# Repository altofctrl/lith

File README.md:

## the oldest tool we know how to make

1931, Olduvai Gorge, Tanzania.

In a ravein cut through the Serengeti plain, researchers discovered stones that had been deliberately broken, intentionally struck with larger ones till sharp flakes came away. They call this era of tool making **Oldowan** after the gorge, and it has examples dating back to 2.6 million years ago.

A stone chopper is the simplest
thing that is unmistakably *made*, and for most of the time there have been
hominins at all, it was the most complicated thing anyone could do. Making one
is harder than it looks: you have to read the stone, find a platform, and strike
at an angle that takes a flake off rather than shattering the core. People who
try it without being shown mostly fail.

These tools are some of the simplest things that can be unmistakably *made*, for most of the time we've been about it was the most complicated thing anyone could do.
However making one takes some skill, finding the right stone, striking the right angle with enough force to flake off instead of shatter.

_Knapping_ is difficult enough to learn, and
useless enough to invent from scratch, that it had to be **taught**. A 2015
experiment by Morgan and colleagues found that transmitting Oldowan technique
got measurably better as you moved from letting people watch, to gestural
teaching, to teaching with words.[1] Their argument is that toolmaking and
language leaned on each other as they grew. The first thing we made and the
first thing we said may have been the same conversation: *here, hold it like
this.*

## what lith is

lith is a small desk object: an ESP32-S3, a 320x170 display, a scroll wheel,
two key switches and a vibration motor in a printed shell. Out of the box it is
a pomodoro timer. That is the shape it arrives in, not the shape it has to keep.

The name is from *líthos*, stone. You reconfigure it by **knapping** it: you
describe what you want it to be, an agent called Oldowan writes the firmware,
and it is flashed to the device from the browser. The tools people make get
shared in the knappery.

The reason it is built this way is Bandura's: self-efficacy, the belief that
you can actually do the thing, is built most strongly from **mastery
experience**, and after that from watching someone like you succeed.[2] Which
role model, and for whom, turns out to matter: a systematic review by
Gladstone and Cimpian found that the effect depends on how *similar* the model
seems and how *attainable* their success looks, and that a model whose success
reads as out of reach can demotivate rather than encourage.[3] lith is
arranged so a beginner gets all three. You *watch* it be made through short form video content. You *make* one, by building it from its constituent parts. Then you *use* the
thing you made, on your desk, developing your own firmware by hand or with Oldowan's help.

[point on how overcoming the first hurdle towards that mastery experience improves continutity] 

## what is in here

| | |
|---|---|
| [`firmware/`](firmware/) | The PlatformIO project that runs on the device. The pomodoro timer, the metaball fluid renderer, the display and input drivers. This is the stock shape lith ships in. |
| [`website/`](website/) | [lith.vidalion.co](https://lith.vidalion.co). The scroll-driven homepage, the onboarding walkthrough, the knapping bench and the knappery, every earlier version of them, and the Oldowan agent that writes firmware from a conversation. |
| [`research/`](research/) | Two studies run against the agent: whether the model tier behind Oldowan changes the quality of what it builds, and what the providers cost and how long they take. |

### website/

- `site/`: the four pages as they are served. `index.html` is the scroll-driven
  homepage, `onboarding.html` the walkthrough a new lith arrives with,
  `knapp.html` the knapping bench where you talk to Oldowan and flash the
  result from the browser, and `knappery.html` the shelf of builds other
  people have published.
- `agent/`: Oldowan. `oldowan.py` is the conversation and prompt layer,
  `builder.py` compiles and repairs the sketch it produces, `knappery.py` is the
  sharing side. `providers.json` selects the model; keys come from a
  `secrets.json` that is not in this repo.
- `versions/`: dated snapshots of every earlier version of the pages, back
  to before the renders existed.
- `assets/`: the WebP sequences the site actually serves.

### research/

- `ui-judge/`: 19 firmware builds from 11 models across 5 providers, compiled,
  rendered on the simulator and judged. The headline is that the **repair loop
  matters more than the model tier**: first-pass compile rate was 26%, and the
  builder's own repair passes took it to 79%.
- `provider-cost-latency/`: wall-clock latency and list price across the
  providers Oldowan can run on, replayed through one real 3-turn conversation.

Both are written up with their figures in
[`research/README.md`](research/README.md).

## references

1. Morgan, T. J. H., Uomini, N. T., Rendell, L. E., et al. (2015). Experimental
   evidence for the co-evolution of hominin tool-making teaching and language.
   *Nature Communications*, 6, 6029. https://doi.org/10.1038/ncomms7029

2. Bandura, A. (1997). *Self-Efficacy: The Exercise of Control*. W. H. Freeman.

3. Gladstone, J. R., & Cimpian, A. (2021). Which role models are effective for
   which students? A systematic review and four recommendations for maximizing
   the effectiveness of role models in STEM. *International Journal of STEM
   Education*, 8(1), 59. https://doi.org/10.1186/s40594-021-00315-x

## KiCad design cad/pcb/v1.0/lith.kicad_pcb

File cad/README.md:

# cad

Mechanical and PCB source for lith v1.

    lith_assy_v1.step        full assembly, mechanical solids and PCB copper
    mechanical/
      lith_assy_v1.f3d       the Fusion source
      enclosure_top.stl      top shell, display cutout and switch plate
      enclosure_bottom.stl   base
      encoder_wheel.stl      scroll wheel
      keycap.stl             keycap, one per switch
    pcb/
      v1.0/                  KiCad project, first board
      v1.1/                  KiCad project, second board
        lith.kicad_sch       schematic
        lith.kicad_pcb       layout
        jlcpcb/gerber/       the fab output that was sent to JLC
        customs.pretty/      footprints drawn for this board

Each board folder is a self-contained KiCad project: it carries its own
`fp-lib-table` / `sym-lib-table` and the non-stock symbols, footprints and
connector 3D models the design pulls in, so it opens without the rest of the
library set.

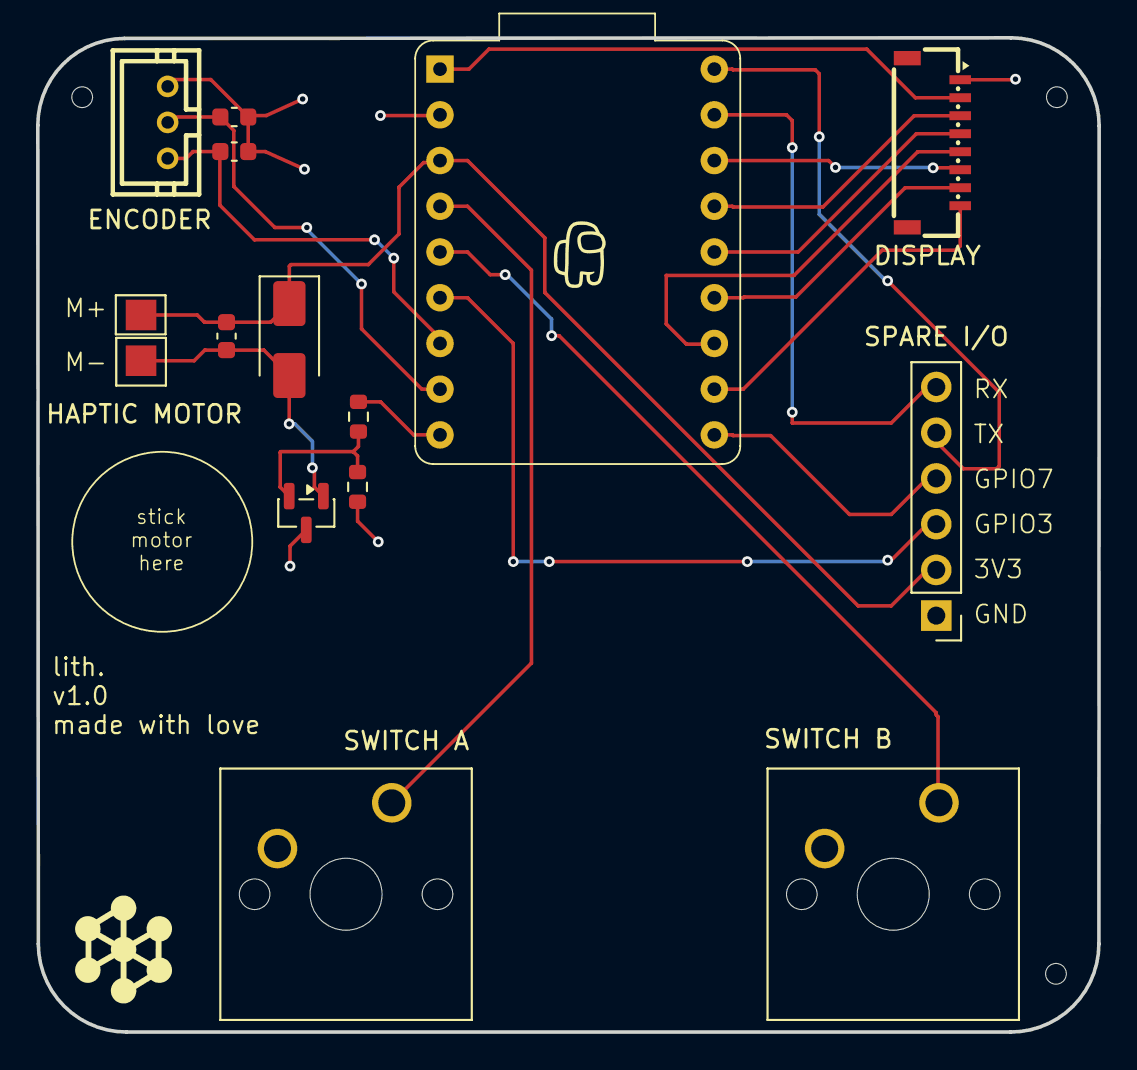
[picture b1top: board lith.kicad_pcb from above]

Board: 2 copper layers, 59.0 x 55.2 mm, 14 parts (0 on the bottom side), 20 nets.

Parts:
C1, C2, C3: 100n; C_0603_1608Metric
D1: D; D_SMA
DISPLAY: Conn_01x08_Socket; CONN-SMD_8P-P1.00_XUNPU_WAFER-100L-8P
ENCODER: RotaryEncoder; CONN-TH_3P-P2.00_HX-2.0MM-3P-ZZ-MS
HAPTIC MOTOR: Motor_DC; PinHeader_1x02_P2.54mm_Vertical
Q1: NPN; SOT-23
R1: 1k; R_0603_1608Metric
R2: 10k; R_0603_1608Metric
SPARE I/O: Conn_01x06_Socket; PinHeader_1x06_P2.54mm_Vertical
SWITCH A: SW_Push; SW_Cherry_MX_1.00u_PCB
SWITCH B: SW_Push; SW_Cherry_MX_1.00u_PCB
U1: ESP32-S3-Zero; Waveshare-ESP32-S3-Zero

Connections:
+3V3: C3.1, D1.1 (K), HAPTIC MOTOR.1 (+), SPARE I/O.2, U1.3 (3V3(OUT))
+5V: DISPLAY.2, U1.1 (VDD)
DISP_BLK: DISPLAY.8, U1.11 (GPIO8)
DISP_CS: DISPLAY.7, U1.13 (GPIO10)
DISP_DC: DISPLAY.6, U1.16 (GPIO13)
DISP_RES: DISPLAY.5, U1.12 (GPIO9)
DISP_SCL: DISPLAY.3, U1.15 (GPIO12)
DISP_SDA: DISPLAY.4, U1.14 (GPIO11)
ENCODER_A: C1.1, ENCODER.3, U1.7 (GPIO4)
ENCODER_B: C2.1, ENCODER.2, U1.8 (GPIO5)
GND: C1.2, C2.2, DISPLAY.1, ENCODER.1, Q1.3 (E), R2.2, SPARE I/O.1, SWITCH A.2, SWITCH B.2, U1.2 (GND)
GPIO3: SPARE I/O.3, U1.6 (GPIO3)
GPIO7: SPARE I/O.4, U1.10 (GPIO7)
MOTOR_PWM: R1.1, U1.9 (GPIO6)
Q_B: Q1.2 (B), R1.2, R2.1
Q_C: C3.2, D1.2 (A), HAPTIC MOTOR.2 (-), Q1.1 (C)
RX: SPARE I/O.6, U1.17 (RX)
SW1: SWITCH A.1, U1.4 (GPIO1)
SW2: SWITCH B.1, U1.5 (GPIO2)
TX: SPARE I/O.5, U1.18 (TX)
